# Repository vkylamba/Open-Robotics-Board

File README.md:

# Open-Robotics-Board
Open robotics development board

## Board Specifications
1. ATmega2560 microcontroller.
2. 6 L293d motor drives chips with terminal blocks to connect motor/LEDs.
3. Ports to connect WiFi, and GPRS.
4. On board 16x2 LCD.
5. On board USB port to program the board, and for serial communication.
6. Can be power from 5V-35V.
7. 5 analog ports with female barrel jacks(2 of them can accept high voltages, and are isolated).

## Board Image

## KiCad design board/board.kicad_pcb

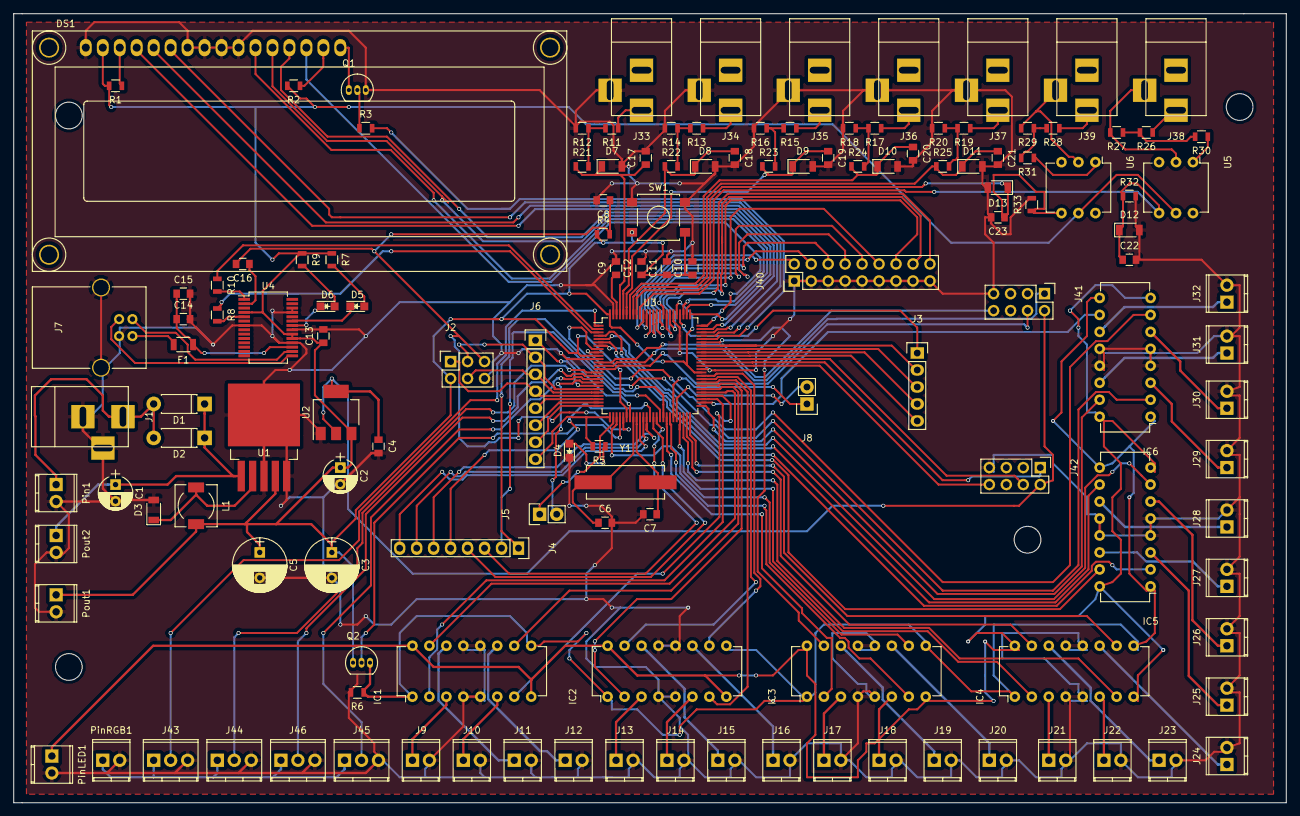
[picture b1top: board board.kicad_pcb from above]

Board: 2 copper layers, 190.5 x 118.1 mm, 139 parts (0 on the bottom side), 157 nets.

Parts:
C1: 40V, 100uF; CP_Radial_D5.0mm_P2.50mm
C2: 220uF; CP_Radial_D5.0mm_P2.50mm
C3: CP15V, 1000uF; CP_Radial_D8.0mm_P3.80mm
C4: 22uF; C_0805
C5: 5V, 1000uF; CP_Radial_D8.0mm_P3.80mm
C6: 22pF; C_0805
C7: 22p; C_0805
C8, C9, C13, C14, C15, C16, C17, C18, C19, C20, C21, C22, C23: 100n; C_0805
C10, C11, C12: 100nF; C_0805
D1, D2: 1N4007; D_DO-41_SOD81_P7.62mm_Horizontal
D3: 1N5822; D_1206
D4: LED_ALT; LED_0805
D5: Rx; LED_0805
D6: TX; LED_0805
D7, D8, D9, D10, D11, D12, D13: 1n4733a; D_1206
DS1: LCD16X2; WC1602A
F1: 500mA; R_1206
IC1, IC2, IC3, IC4, IC5, IC6: L293D; DIP-16_W7.62mm
J1: BARREL_JACK
J2: ICSP; Socket_Strip_Straight_2x03
J3: Port J; Pin_Header_Straight_1x05
J4: Port L; Pin_Header_Straight_1x08
J5: Port H; Pin_Header_Straight_1x02
J6: Port C; Pin_Header_Straight_1x08
J7: USB_B
J8: Comm; Pin_Header_Straight_1x02
J9: LED_OUT1; TerminalBlock_Pheonix_MPT-2.54mm_2pol
J10: LED_OUT2; TerminalBlock_Pheonix_MPT-2.54mm_2pol
J11: LED_OUT3; TerminalBlock_Pheonix_MPT-2.54mm_2pol
J12: LED_OUT4; TerminalBlock_Pheonix_MPT-2.54mm_2pol
J13: LED_OUT5; TerminalBlock_Pheonix_MPT-2.54mm_2pol
J14: LED_OUT6; TerminalBlock_Pheonix_MPT-2.54mm_2pol
J15: LED_OUT7; TerminalBlock_Pheonix_MPT-2.54mm_2pol
J16: LED_OUT8; TerminalBlock_Pheonix_MPT-2.54mm_2pol
J17: LED_OUT9; TerminalBlock_Pheonix_MPT-2.54mm_2pol
J18: LED_OUT10; TerminalBlock_Pheonix_MPT-2.54mm_2pol
J19: LED_OUT11; TerminalBlock_Pheonix_MPT-2.54mm_2pol
J20: LED_OUT12; TerminalBlock_Pheonix_MPT-2.54mm_2pol
J21: LED_OUT13; TerminalBlock_Pheonix_MPT-2.54mm_2pol
J22: LED_OUT14; TerminalBlock_Pheonix_MPT-2.54mm_2pol
J23: LED_OUT15; TerminalBlock_Pheonix_MPT-2.54mm_2pol
J24: LED_OUT16; TerminalBlock_Pheonix_MPT-2.54mm_2pol
J25: LED_OUT17; TerminalBlock_Pheonix_MPT-2.54mm_2pol
J26: LED_OUT18; TerminalBlock_Pheonix_MPT-2.54mm_2pol
J27: LED_OUT19; TerminalBlock_Pheonix_MPT-2.54mm_2pol
J28: LED_OUT20; TerminalBlock_Pheonix_MPT-2.54mm_2pol
J29: LED_OUT21; TerminalBlock_Pheonix_MPT-2.54mm_2pol
J30: LED_OUT22; TerminalBlock_Pheonix_MPT-2.54mm_2pol
J31: LED_OUT23; TerminalBlock_Pheonix_MPT-2.54mm_2pol
J32: LED_OUT24; TerminalBlock_Pheonix_MPT-2.54mm_2pol
J33: Ain-0; BARREL_JACK
J34: Ain-1; BARREL_JACK
J35: Ain-2; BARREL_JACK
J36: Ain-3; BARREL_JACK
J37: Ain-4; BARREL_JACK
J38: Ain-6; BARREL_JACK
J39: Ain-5; BARREL_JACK
J40: CONN_02X09; Pin_Header_Straight_2x09
J41: WiFi; Pin_Header_Straight_2x04
J42: GPRS; Pin_Header_Straight_2x04
J43: RGB1; TerminalBlock_Pheonix_MPT-2.54mm_3pol
J44: RGB2; TerminalBlock_Pheonix_MPT-2.54mm_3pol
J45: RGB4; TerminalBlock_Pheonix_MPT-2.54mm_3pol
J46: RGB3; TerminalBlock_Pheonix_MPT-2.54mm_3pol
L1: 33uH, 3A; Choke_SMD_6.3x6.3_H3
Pin1: Pin; TerminalBlock_Pheonix_MPT-2.54mm_2pol
PinLED1: LED Vcc; TerminalBlock_Pheonix_MPT-2.54mm_2pol
PinRGB1: RGB Vcc; TerminalBlock_Pheonix_MPT-2.54mm_2pol
Pout1: 5V; TerminalBlock_Pheonix_MPT-2.54mm_2pol
Pout2: Vcc Out; TerminalBlock_Pheonix_MPT-2.54mm_2pol
Q1, Q2: BC547; TO-92_Inline_Narrow_Oval
R1, R3, R5, R7, R8, R9, R10, R21, R22, R23, R24, R25: 1k; R_0805
R2, R6: 5k; R_0805
R4, R12, R14, R16, R18, R20, R32, R33: 10k; R_0805
R11, R13, R15, R17, R19, R26, R28: 100k; R_0805
R27, R29: 50k; R_0805
R30, R31: 220k; R_0805
SW1: reset; SW_SPST_B3S-1000
U1: LM2596S-5; TO-263-5Lead
U2: AMS1117; SOT-223-3Lead_TabPin2
U3: ATMEGA1280-16AU; TQFP-100_14x14mm_Pitch0.5mm
U4: FT232RL; SSOP-28_5.3x10.2mm_Pitch0.65mm
U5, U6: 4n25; DIP-6_W7.62mm
Y1: 16Mhz; Crystal_HC49-SD_SMD

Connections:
+3V3: C4.1, J41.2, J42.2, U2.2
+5V: C2.1, C3.1, C5.1, C10.1, C11.1, C12.1, C13.1, DS1.2, J2.2, L1.2, Pout1.1, Q2.1, R1.2, R2.2, R4.1, R7.1, R9.1, SW1.2, U1.4, U2.3, U3.10, U3.31, U3.61, U3.80, U3.100, U4.4, U4.19, U4.20, U5.5, U6.5
/LED_DRIVER1/LED_OUT3: IC1.14, J11.1
/LED_DRIVER1/LED_OUT4: IC1.11, J12.1
/LED_DRIVER2/LED_OUT7: IC2.14, J15.1
/LED_DRIVER2/LED_OUT8: IC2.11, J16.1
/LED_DRIVER3/LED_OUT11: IC3.14, J19.1
/LED_DRIVER3/LED_OUT12: IC3.11, J20.1
/LED_DRIVER4/LED_OUT15: IC4.14, J23.1
/LED_DRIVER4/LED_OUT16: IC4.11, J24.1
/LED_DRIVER5/LED_OUT19: IC5.14, J27.1
/LED_DRIVER5/LED_OUT20: IC5.11, J28.1
/LED_DRIVER6/LED_OUT23: IC6.14, J31.1
/LED_DRIVER6/LED_OUT24: IC6.11, J32.1
/Vin: D1.2, D2.2, J1.1, Pin1.1
/controller/ENABLE_LED_DRIVERS: Q2.2, U3.29
/controller/MISO: J2.1, J6.4, U3.22
/controller/MOSI: J2.4, J6.3, U3.21
/controller/RX0: J8.1, U3.45
/controller/SCK: J2.3, J6.2, U3.20
/controller/TX0: J8.2, U3.46
AIN0: C17.1, D7.1, R21.1, U3.97
AIN1: C18.1, D8.1, R22.1, U3.96
AIN2: C19.1, D9.1, R23.1, U3.95
AIN3: C20.1, D10.1, R24.1, U3.94
AIN4: C21.1, D11.1, R25.1, U3.93
AIN5: C23.1, D13.1, R33.1, U3.92, U6.4
AIN6: C22.1, D12.1, R32.1, U3.91, U5.4
AIN7: J40.2, U3.90
AIN8: J40.4, U3.89
AIN9: J40.6, U3.88
AIN10: J40.8, U3.87
AIN11: J40.10, U3.86
AIN12: J40.12, U3.85
AIN13: J40.14, U3.84
AIN14: J40.16, U3.83
AIN15: J40.18, U3.82
FTDI_RX: R8.1, U3.3
FTDI_TX: R10.1, U3.2
GND: C1.2, C2.2, C3.2, C4.2, C5.2, C6.2, C7.2, C8.2, C9.2, C10.2, C11.2, C12.2, C13.2, C14.2, C15.2, C17.2, C18.2, C19.2, C20.2, C21.2, C22.2, C23.2, D3.2, D4.1, D7.2, D8.2, D9.2, D10.2, D11.2, D12.2, D13.2, DS1.1, DS1.7, DS1.8, DS1.9, DS1.10, IC1.4, IC1.5, IC1.12, IC1.13, IC2.4, IC2.5, IC2.12, IC2.13, IC3.4, IC3.5, IC3.12, IC3.13, IC4.4, IC4.5, IC4.12, IC4.13, IC5.4, IC5.5, IC5.12, IC5.13, IC6.4, IC6.5, IC6.12, IC6.13, J1.2, J1.3, J2.6, J7.4, J7.5, J9.2, J10.2, J11.2, J12.2, J13.2, J14.2, J15.2, J16.2, J17.2, J18.2, J19.2, J20.2, J21.2, J22.2, J23.2, J24.2, J25.2, J26.2, J27.2, J28.2, J29.2, J30.2, J31.2, J32.2, J33.3, J34.3, J35.3, J36.3, J37.3, J40.1, J40.3, J40.5, J40.7, J40.9, J40.11, J40.13, J40.15, J40.17, J41.7, J42.7, J43.3, J44.3, J45.3, J46.3, Pin1.2, PinLED1.2, PinRGB1.2, Pout1.2, Pout2.2, Q1.3, R6.2, R12.2, R14.2, R16.2, R18.2, R20.2, R32.2, R33.2, SW1.1, U1.3, U1.5, U2.1, U3.11, U3.32, U3.62, U3.81, U3.99, U4.7, U4.18, U4.21, U4.25, U4.26
GPRS_RESET: J42.4, U3.65
GPRS_RX: J42.1, U3.64
GPRS_TX: J42.8, U3.63
LCD_BKLIGHT_CTRL: R3.2, U3.71
LCD_DATA1: DS1.11, U3.78
LCD_DATA2: DS1.12, U3.77
LCD_DATA3: DS1.13, U3.76
LCD_DATA4: DS1.14, U3.75
LCD_ENABLE: DS1.6, U3.72
LCD_RS: DS1.4, U3.74
LCD_RW: DS1.5, U3.73
LED1: IC1.2, U3.53
LED2: IC1.7, U3.54
LED3: IC1.15, U3.55
LED4: IC1.10, U3.56
LED5: IC2.2, U3.57
LED6: IC2.7, U3.58
LED7: IC2.15, U3.59
LED8: IC2.10, U3.60
LED9: IC3.2, U3.43
LED10: IC3.7, U3.44
LED11: IC3.15, U3.70
LED12: IC3.10, U3.28
LED13: IC4.2, U3.47
LED14: IC4.7, U3.48
LED15: IC4.15, U3.49
LED16: IC4.10, U3.50
LED17: IC5.2, U3.4
LED18: IC5.7, U3.5
LED19: IC5.15, U3.6
LED20: IC5.10, U3.7
LED21: IC6.2, U3.8
LED22: IC6.7, U3.9
LED23: IC6.15, U3.51
LED24: IC6.10, U3.52
LED_DRIVER1.1_EN: IC1.1, IC1.9, IC2.1, IC2.9, IC3.1, IC3.9, IC4.1, IC4.9, IC5.1, IC5.9, IC6.1, IC6.9, Q2.3, R6.1
LED_VCC: IC1.8, IC1.16, IC2.8, IC2.16, IC3.8, IC3.16, IC4.8, IC4.16, IC5.8, IC5.16, IC6.8, IC6.16, PinLED1.1
unnamed: C6.1, U3.33, Y1.1
unnamed: C7.1, U3.34, Y1.2
unnamed: C9.1, U3.98
unnamed: C14.1, C15.1, F1.1, U4.17
unnamed: C16.1, U4.2
unnamed: D3.1, L1.1, U1.2
unnamed: D4.2, R5.1
unnamed: D5.1, U4.23
unnamed: D5.2, R7.2
unnamed: D6.1, U4.22
unnamed: D6.2, R9.2
unnamed: DS1.3, R1.1
unnamed: DS1.15, R2.1
unnamed: DS1.16, Q1.1
unnamed: F1.2, J7.1
unnamed: IC1.3, J9.1
unnamed: IC1.6, J10.1
unnamed: IC2.3, J13.1
unnamed: IC2.6, J14.1
unnamed: IC3.3, J17.1
unnamed: IC3.6, J18.1
unnamed: IC4.3, J21.1
unnamed: IC4.6, J22.1
unnamed: IC5.3, J25.1
unnamed: IC5.6, J26.1
unnamed: IC6.3, J29.1
unnamed: IC6.6, J30.1
unnamed: J3.1, U3.79
unnamed: J3.2, U3.69
unnamed: J3.3, U3.68
unnamed: J3.4, U3.67
unnamed: J3.5, U3.66
unnamed: J4.1, U3.42
unnamed: J4.2, U3.41
unnamed: J4.3, U3.40
unnamed: J4.4, U3.39
unnamed: J4.5, U3.38
unnamed: J4.6, U3.37
unnamed: J4.7, U3.36
unnamed: J4.8, U3.35
unnamed: J5.1, U3.27
unnamed: J5.2, U3.18
unnamed: J6.1, U3.19
unnamed: J6.5, U3.23
unnamed: J6.6, U3.24
unnamed: J6.7, U3.25
unnamed: J6.8, R5.2, U3.26
unnamed: J7.2, U4.16
unnamed: J7.3, U4.15
unnamed: J33.1, R11.1
unnamed: J34.1, R13.1
unnamed: J35.1, R15.1
unnamed: J36.1, R17.1
unnamed: J37.1, R19.1
unnamed: J38.1, R26.1
unnamed: J38.3, R27.2, U5.2
unnamed: J39.1, R28.1
unnamed: J39.3, R29.2, U6.2
unnamed: Q1.2, R3.1
unnamed: R8.2, U4.5
unnamed: R10.2, U4.1
unnamed: R11.2, R12.1, R21.2
unnamed: R13.2, R14.1, R22.2
unnamed: R15.2, R16.1, R23.2
unnamed: R17.2, R18.1, R24.2
unnamed: R19.2, R20.1, R25.2
unnamed: R26.2, R27.1, R30.2
unnamed: R28.2, R29.1, R31.2
unnamed: R30.1, U5.1
unnamed: R31.1, U6.1
RESET: C8.1, C16.2, J2.5, R4.2, U3.30
RGB_LED1: J43.2, U3.1
RGB_LED2: J44.2, U3.15
RGB_LED3: J46.2, U3.16
RGB_LED4: J45.2, U3.17
RGB_VCC: J43.1, J44.1, J45.1, J46.1, PinRGB1.1
VCC: C1.1, D1.1, D2.1, Pout2.1, U1.1
WiFi_RESET: J41.4, U3.14
WiFi_RX: J41.1, U3.13
WiFi_TX: J41.8, U3.12

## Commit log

2017-09-04 Added board design files
2017-12-27 Added Board Image
